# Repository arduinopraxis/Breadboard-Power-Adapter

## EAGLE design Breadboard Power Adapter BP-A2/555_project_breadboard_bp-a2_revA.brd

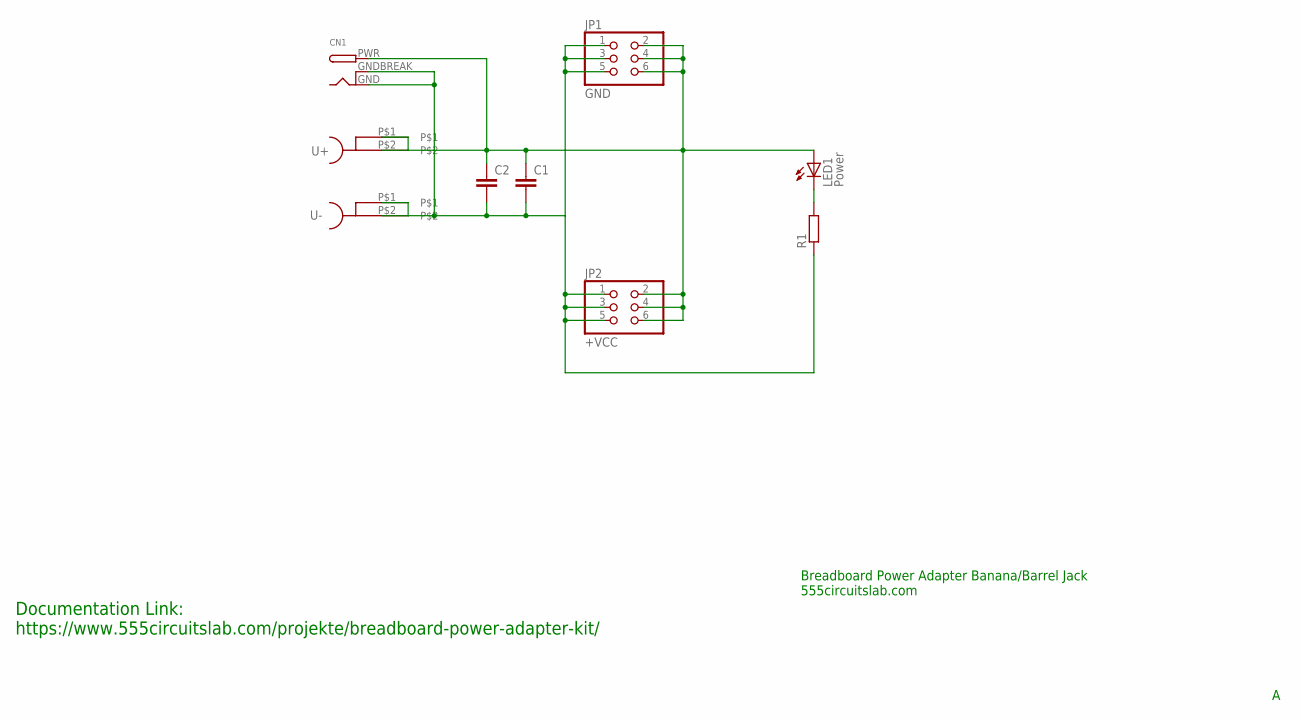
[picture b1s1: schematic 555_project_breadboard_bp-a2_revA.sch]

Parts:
C1, C2: C-EU025-024X044; C025-024X044
CN1: DCBARRELPTH; DCJACK_2MM_PTH
JP1: GND; 2X03
JP2: +VCC; 2X03
LED1: Power; LED5MM
R1: R-EU_0204/7; 0204/7
U+: PCB-BANANA
U-: PCB-BANANA

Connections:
GND: C1.2, C2.2, CN1.GND, CN1.GNDBREAK, JP1.1, JP1.3, JP1.5, JP2.1, JP2.3, JP2.5, R1.1, U-.P$1, U-.P$2
unnamed: LED1.K (C), R1.2
VCC: C1.1, C2.1, CN1.PWR, JP1.2, JP1.4, JP1.6, JP2.2, JP2.4, JP2.6, LED1.A, U+.P$1, U+.P$2

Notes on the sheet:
Breadboard Power Adapter Banana/Barrel Jack 555circuitslab.com
Documentation Link: https://www.555circuitslab.com/projekte/breadboard-power-adapter-kit/

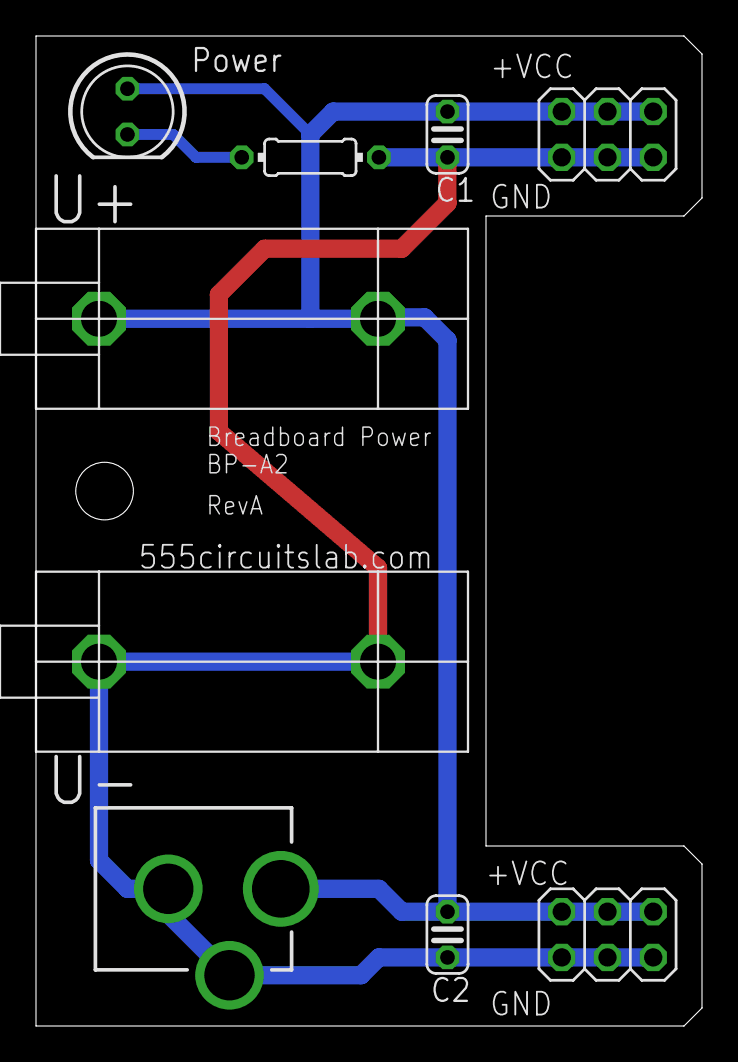
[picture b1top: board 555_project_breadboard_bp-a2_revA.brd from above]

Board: 2 copper layers, 37.0 x 55.0 mm, 9 parts (0 on the bottom side), 3 nets.
